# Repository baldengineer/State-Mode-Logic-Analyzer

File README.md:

Every logic analyzer available today samples asychrnously. On slower systems this is needlessly wasteful.

This logic analyzer works as a state mode capture. A clock on the device-under-test (DUT) drives the capture.

More to come...

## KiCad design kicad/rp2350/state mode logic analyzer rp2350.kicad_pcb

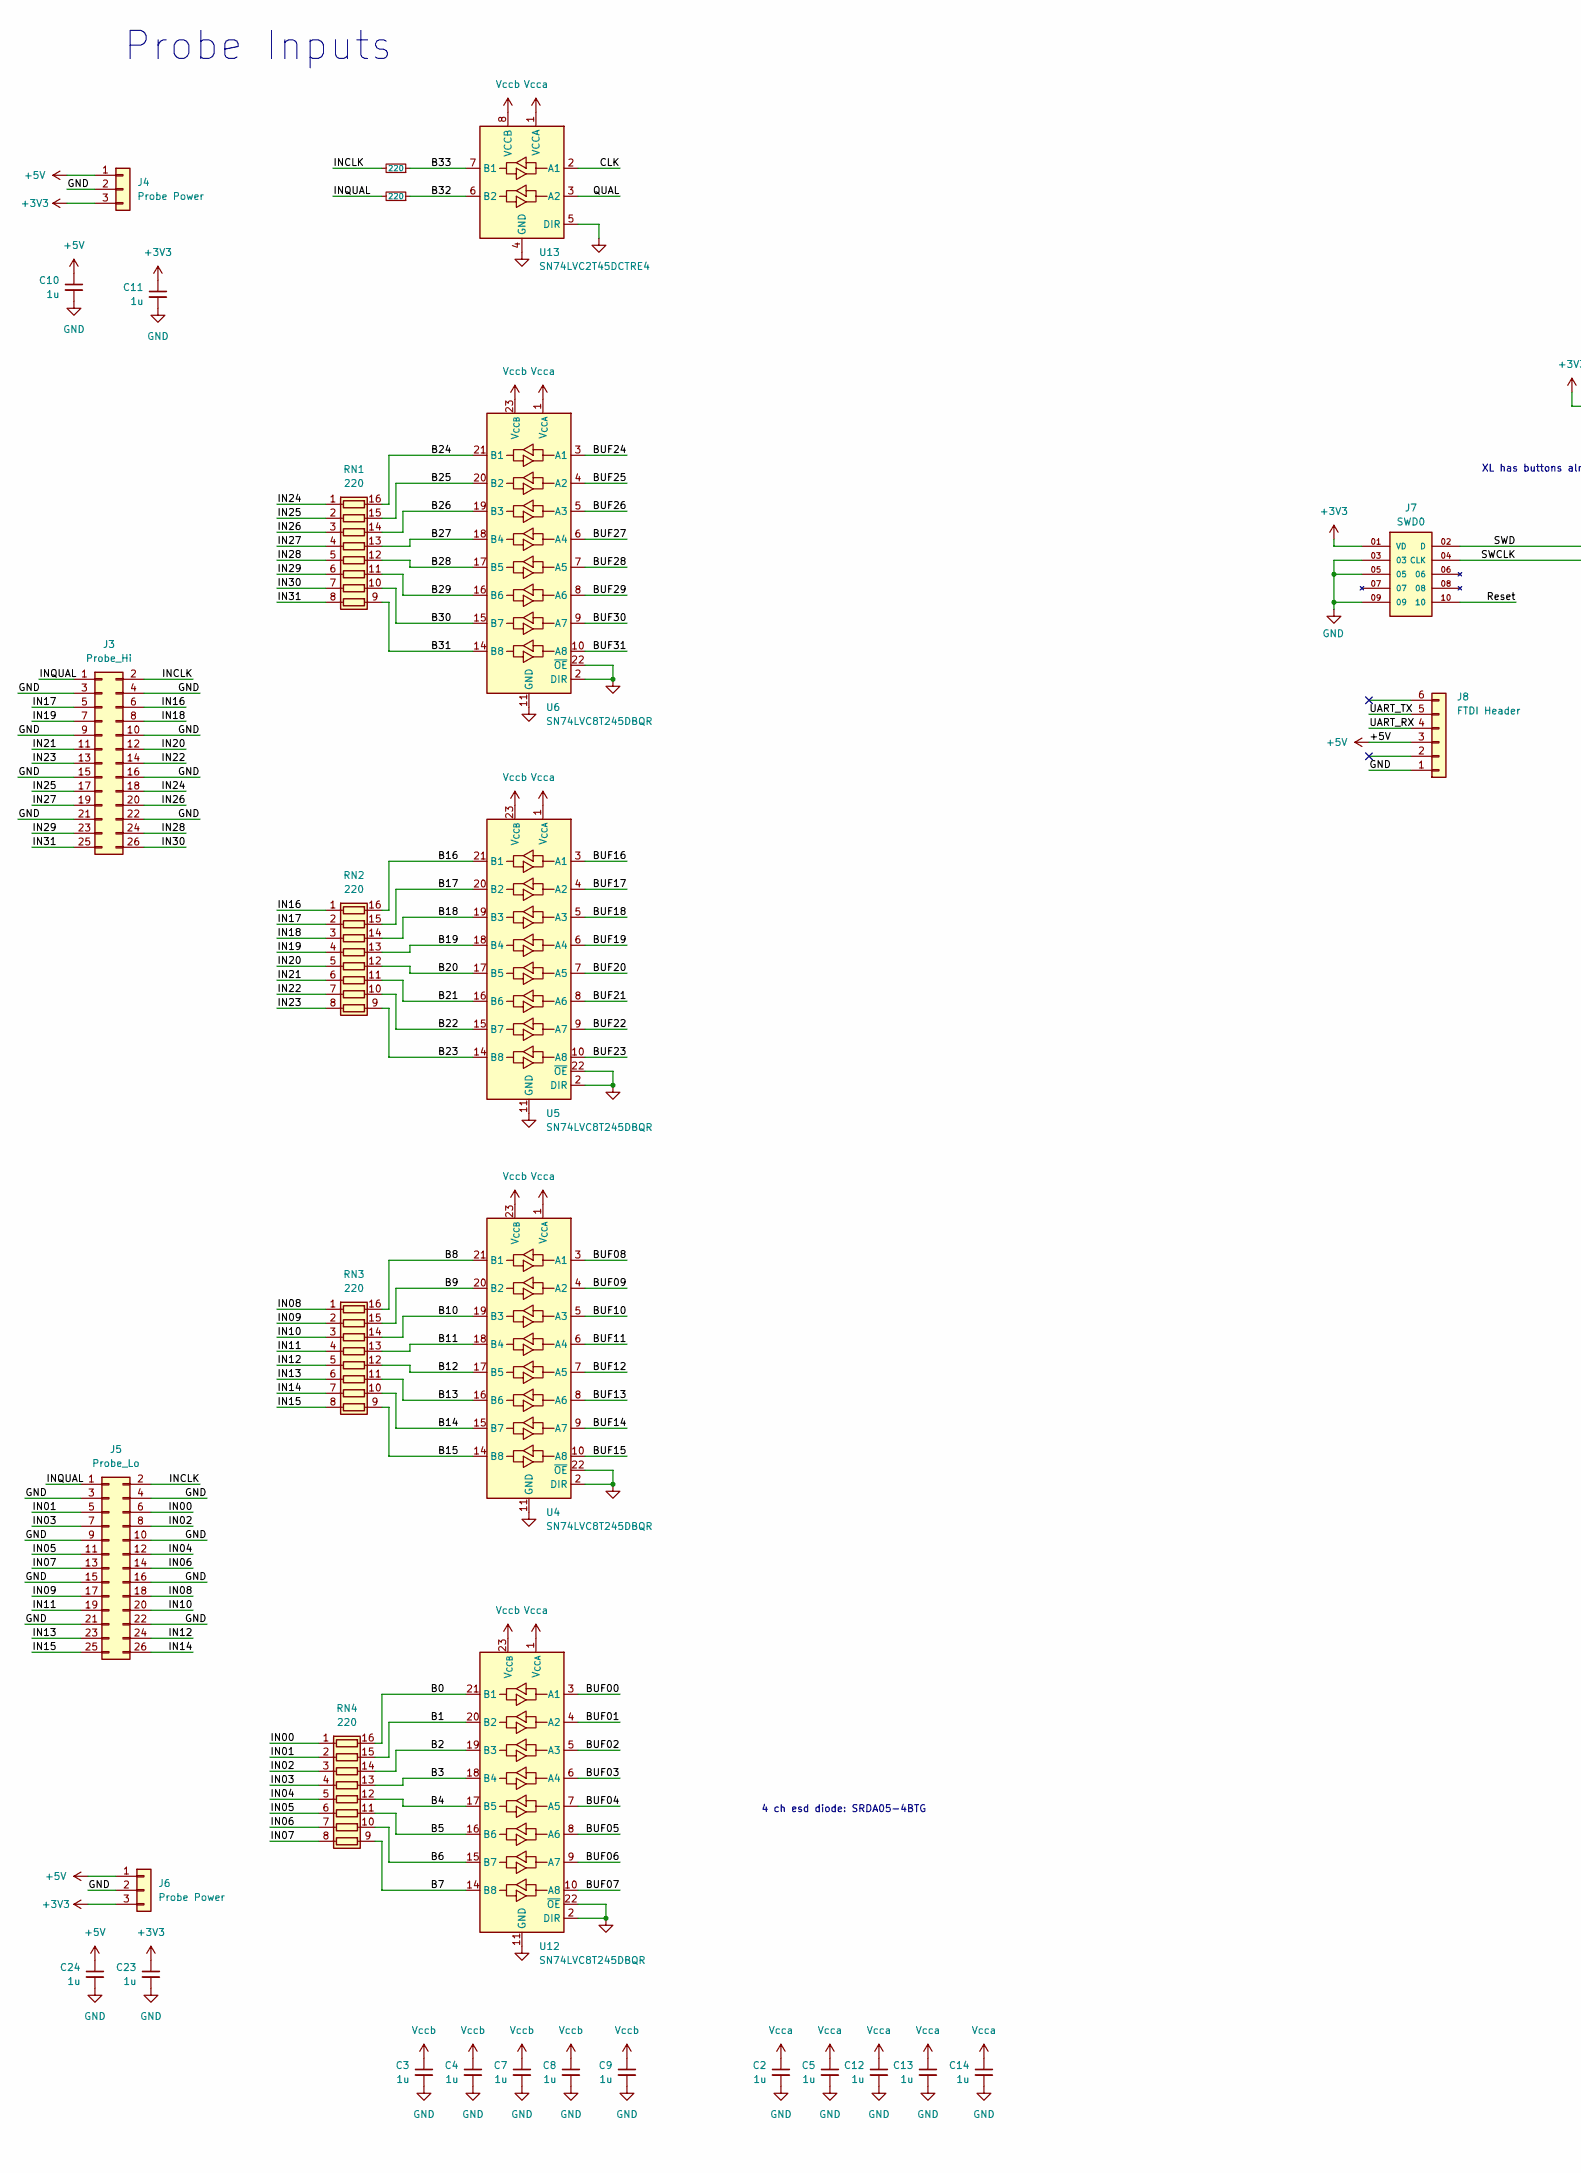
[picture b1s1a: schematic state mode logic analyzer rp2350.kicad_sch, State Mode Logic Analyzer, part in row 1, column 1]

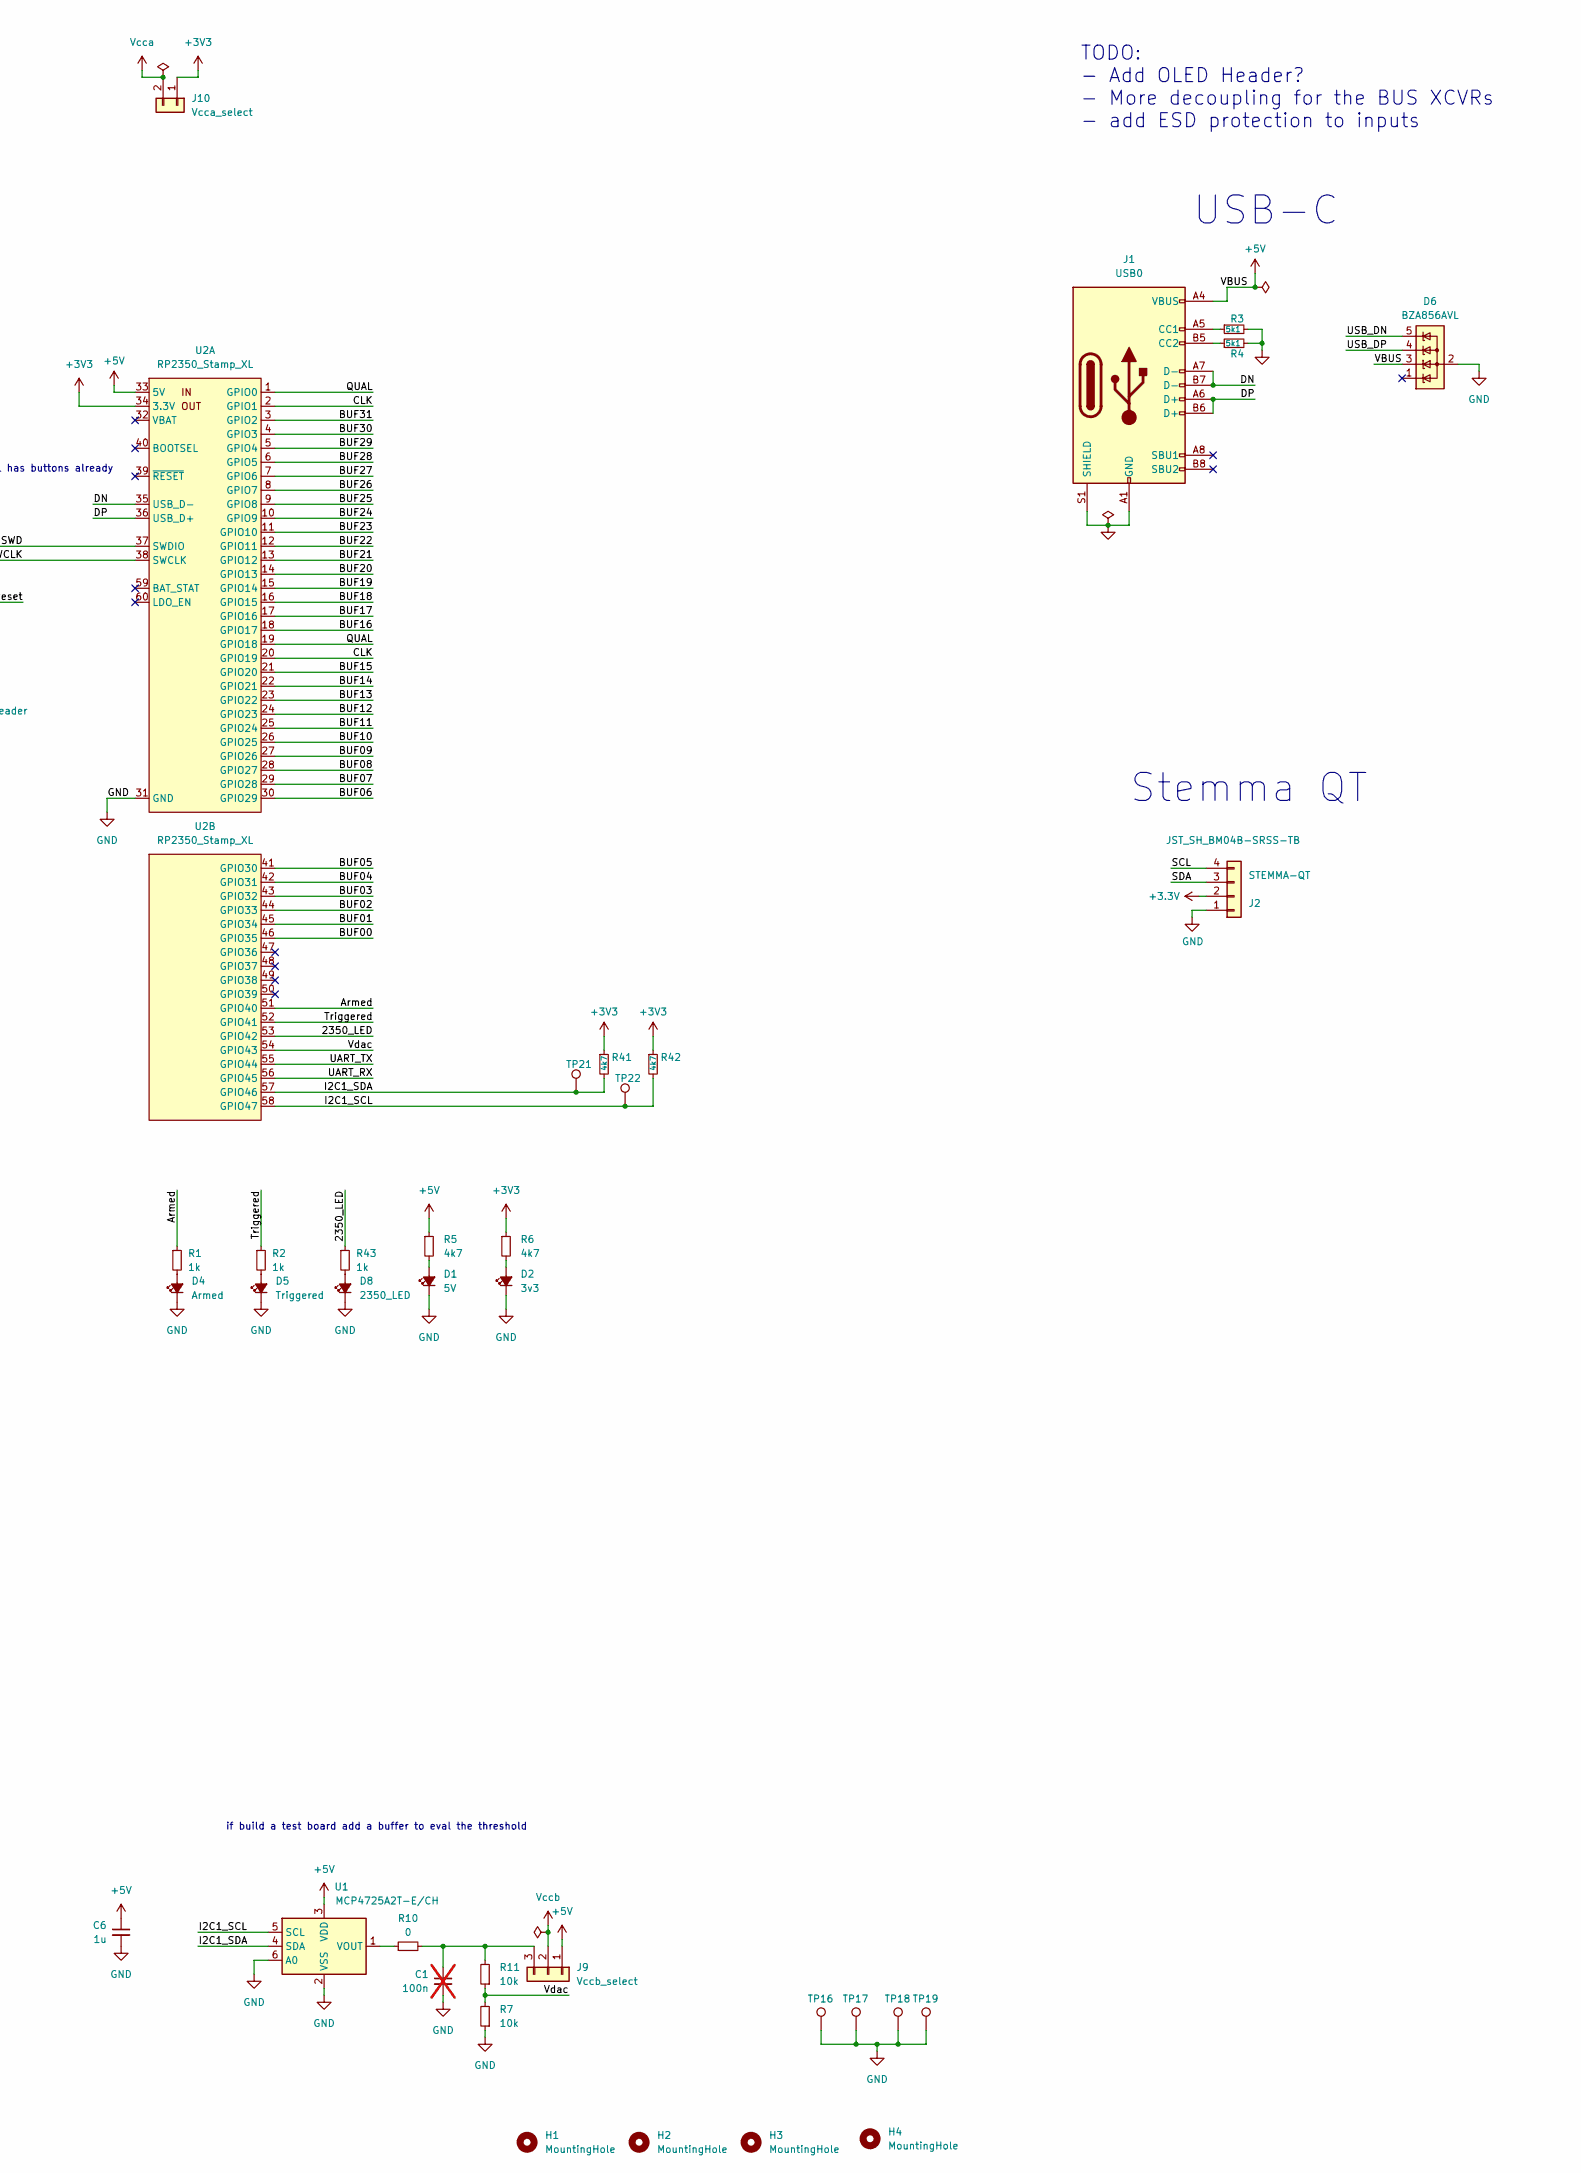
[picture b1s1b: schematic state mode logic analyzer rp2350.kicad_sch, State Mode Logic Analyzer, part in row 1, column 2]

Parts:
C1: 100n; C_0603_1608Metric_Pad1.08x0.95mm_HandSolder; not fitted
C2, C3, C4, C5, C6, C7, C8, C9, C10, C11, C12, C13, C14, C23, C24: 1u; C_0603_1608Metric_Pad1.08x0.95mm_HandSolder
D1: 5V; LED_1206_3216Metric_Pad1.42x1.75mm_HandSolder
D2: 3v3; LED_1206_3216Metric_Pad1.42x1.75mm_HandSolder
D4: Armed; LED_1206_3216Metric_Pad1.42x1.75mm_HandSolder
D5: Triggered; LED_1206_3216Metric_Pad1.42x1.75mm_HandSolder
D6: BZA856AVL; SOT-353_SC-70-5
D8: 2350_LED; LED_1206_3216Metric_Pad1.42x1.75mm_HandSolder
H1, H2, H3, H4: MountingHole; MountingHole_2.7mm
J1: USB0; USB_C_Receptacle_GCT_USB4105-xx-A_16P_TopMnt_Horizontal
J2: JST_SH_BM04B-SRSS-TB; JST_SH_BM04B-SRSS-TB_1x04-1MP_P1.00mm_Vertical
J3: Probe_Hi; PinHeader_2x13_P2.54mm_Vertical
J4, J6: Probe Power; PinHeader_1x03_P2.54mm_Vertical
J5: Probe_Lo; PinHeader_2x13_P2.54mm_Vertical
J7: SWD0; SAMTEC_FTSH-105-XX-X-DV; PARTREV H
J8: FTDI Header; PinSocket_1x06_P2.54mm_Vertical
J9: Vccb_select; PinHeader_1x03_P2.54mm_Vertical
J10: Vcca_select; PinHeader_2x01_P2.54mm_Vertical
R1, R2, R43: 1k; R_0603_1608Metric_Pad0.98x0.95mm_HandSolder
R3, R4: 5k1; R_0603_1608Metric_Pad0.98x0.95mm_HandSolder
R5, R6, R41, R42: 4k7; R_0603_1608Metric_Pad0.98x0.95mm_HandSolder
R7, R11: 10k; R_0603_1608Metric
R10: 0; R_0603_1608Metric
R73, R74: 220; R_0603_1608Metric
RN1, RN2, RN3, RN4: YC248-FR-07220RL; R_Array_Convex_8x0602
TP16, TP17, TP18, TP19, TP21, TP22: TestPoint_Harwin; Harwin-S1751-46-Test-Point
U1: MCP4725A2T-E/CH; SOT-23-6
U2: RP2350_Stamp_XL; RP2xxx_Stamp_XL_THT
U4, U5, U6, U12: SN74LVC8T245DBQR; SSOP-24_3.9x8.7mm_P0.635mm
U13: SN74LVC2T45DCTRE4; SSOP-8_2.95x2.8mm_P0.65mm

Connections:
+3.3V: J2.2
+3V3: C11.1, C23.1, J4.3, J6.3, J7.01 (VD), J10.1, R6.1, R41.1, R42.1, U2.34 (3.3V)
+5V: C6.1, C10.1, C24.1, D6.3 (K), J1.A4 (VBUS), J1.A9 (VBUS), J1.B4 (VBUS), J1.B9 (VBUS), J4.1, J6.1, J8.3, J9.1, R5.1, U1.3 (VDD), U2.33 (5V)
/2350_LED: R43.1, U2.53 (GPIO42)
/Armed: R1.1, U2.51 (GPIO40)
/B0: RN4.16 (R1.2), U12.21 (B1)
/B1: RN4.15 (R2.2), U12.20 (B2)
/B2: RN4.14 (R3.2), U12.19 (B3)
/B3: RN4.13 (R4.2), U12.18 (B4)
/B4: RN4.12 (R5.2), U12.17 (B5)
/B5: RN4.11 (R6.2), U12.16 (B6)
/B6: RN4.10 (R7.2), U12.15 (B7)
/B7: RN4.9 (R8.2), U12.14 (B8)
/B8: RN3.16 (R1.2), U4.21 (B1)
/B9: RN3.15 (R2.2), U4.20 (B2)
/B10: RN3.14 (R3.2), U4.19 (B3)
/B11: RN3.13 (R4.2), U4.18 (B4)
/B12: RN3.12 (R5.2), U4.17 (B5)
/B13: RN3.11 (R6.2), U4.16 (B6)
/B14: RN3.10 (R7.2), U4.15 (B7)
/B15: RN3.9 (R8.2), U4.14 (B8)
/B16: RN2.16 (R1.2), U5.21 (B1)
/B17: RN2.15 (R2.2), U5.20 (B2)
/B18: RN2.14 (R3.2), U5.19 (B3)
/B19: RN2.13 (R4.2), U5.18 (B4)
/B20: RN2.12 (R5.2), U5.17 (B5)
/B21: RN2.11 (R6.2), U5.16 (B6)
/B22: RN2.10 (R7.2), U5.15 (B7)
/B23: RN2.9 (R8.2), U5.14 (B8)
/B24: RN1.16 (R1.2), U6.21 (B1)
/B25: RN1.15 (R2.2), U6.20 (B2)
/B26: RN1.14 (R3.2), U6.19 (B3)
/B27: RN1.13 (R4.2), U6.18 (B4)
/B28: RN1.12 (R5.2), U6.17 (B5)
/B29: RN1.11 (R6.2), U6.16 (B6)
/B30: RN1.10 (R7.2), U6.15 (B7)
/B31: RN1.9 (R8.2), U6.14 (B8)
/B32: R74.1, U13.6 (B2)
/B33: R73.1, U13.7 (B1)
/BUF00: U2.46 (GPIO35), U12.3 (A1)
/BUF01: U2.45 (GPIO34), U12.4 (A2)
/BUF02: U2.44 (GPIO33), U12.5 (A3)
/BUF03: U2.43 (GPIO32), U12.6 (A4)
/BUF04: U2.42 (GPIO31), U12.7 (A5)
/BUF05: U2.41 (GPIO30), U12.8 (A6)
/BUF06: U2.30 (GPIO29), U12.9 (A7)
/BUF07: U2.29 (GPIO28), U12.10 (A8)
/BUF08: U2.28 (GPIO27), U4.3 (A1)
/BUF09: U2.27 (GPIO26), U4.4 (A2)
/BUF10: U2.26 (GPIO25), U4.5 (A3)
/BUF11: U2.25 (GPIO24), U4.6 (A4)
/BUF12: U2.24 (GPIO23), U4.7 (A5)
/BUF13: U2.23 (GPIO22), U4.8 (A6)
/BUF14: U2.22 (GPIO21), U4.9 (A7)
/BUF15: U2.21 (GPIO20), U4.10 (A8)
/BUF16: U2.18 (GPIO17), U5.3 (A1)
/BUF17: U2.17 (GPIO16), U5.4 (A2)
/BUF18: U2.16 (GPIO15), U5.5 (A3)
/BUF19: U2.15 (GPIO14), U5.6 (A4)
/BUF20: U2.14 (GPIO13), U5.7 (A5)
/BUF21: U2.13 (GPIO12), U5.8 (A6)
/BUF22: U2.12 (GPIO11), U5.9 (A7)
/BUF23: U2.11 (GPIO10), U5.10 (A8)
/BUF24: U2.10 (GPIO9), U6.3 (A1)
/BUF25: U2.9 (GPIO8), U6.4 (A2)
/BUF26: U2.8 (GPIO7), U6.5 (A3)
/BUF27: U2.7 (GPIO6), U6.6 (A4)
/BUF28: U2.6 (GPIO5), U6.7 (A5)
/BUF29: U2.5 (GPIO4), U6.8 (A6)
/BUF30: U2.4 (GPIO3), U6.9 (A7)
/BUF31: U2.3 (GPIO2), U6.10 (A8)
/CLK: U2.2 (GPIO1), U2.20 (GPIO19), U13.2 (A1)
/DN: J1.A7 (D-), J1.B7 (D-), U2.35 (USB_D-)
/DP: J1.A6 (D+), J1.B6 (D+), U2.36 (USB_D+)
/I2C1_SCL: R42.2, TP22.1, U1.5 (SCL), U2.58 (GPIO47)
/I2C1_SDA: R41.2, TP21.1, U1.4 (SDA), U2.57 (GPIO46)
/IN00: J5.6, RN4.1 (R1.1)
/IN01: J5.5, RN4.2 (R2.1)
/IN02: J5.8, RN4.3 (R3.1)
/IN03: J5.7, RN4.4 (R4.1)
/IN04: J5.12, RN4.5 (R5.1)
/IN05: J5.11, RN4.6 (R6.1)
/IN06: J5.14, RN4.7 (R7.1)
/IN07: J5.13, RN4.8 (R8.1)
/IN08: J5.18, RN3.1 (R1.1)
/IN09: J5.17, RN3.2 (R2.1)
/IN10: J5.20, RN3.3 (R3.1)
/IN11: J5.19, RN3.4 (R4.1)
/IN12: J5.24, RN3.5 (R5.1)
/IN13: J5.23, RN3.6 (R6.1)
/IN14: J5.26, RN3.7 (R7.1)
/IN15: J5.25, RN3.8 (R8.1)
/IN16: J3.6, RN2.1 (R1.1)
/IN17: J3.5, RN2.2 (R2.1)
/IN18: J3.8, RN2.3 (R3.1)
/IN19: J3.7, RN2.4 (R4.1)
/IN20: J3.12, RN2.5 (R5.1)
/IN21: J3.11, RN2.6 (R6.1)
/IN22: J3.14, RN2.7 (R7.1)
/IN23: J3.13, RN2.8 (R8.1)
/IN24: J3.18, RN1.1 (R1.1)
/IN25: J3.17, RN1.2 (R2.1)
/IN26: J3.20, RN1.3 (R3.1)
/IN27: J3.19, RN1.4 (R4.1)
/IN28: J3.24, RN1.5 (R5.1)
/IN29: J3.23, RN1.6 (R6.1)
/IN30: J3.26, RN1.7 (R7.1)
/IN31: J3.25, RN1.8 (R8.1)
/INCLK: J3.2, J5.2, R73.2
/INQUAL: J3.1, J5.1, R74.2
/QUAL: U2.1 (GPIO0), U2.19 (GPIO18), U13.3 (A2)
/Reset: J7.10
/SCL: J2.4
/SDA: J2.3
/SWCLK: J7.04 (CLK), U2.38 (SWCLK)
/SWD: J7.02 (D), U2.37 (SWDIO)
/Triggered: R2.1, U2.52 (GPIO41)
/UART_RX: J8.4, U2.56 (GPIO45)
/UART_TX: J8.5, U2.55 (GPIO44)
/USB_DN: D6.5 (K)
/USB_DP: D6.4 (K)
/Vdac: R7.2, R11.1, U2.54 (GPIO43)
GND: C1.2, C2.2, C3.2, C4.2, C5.2, C6.2, C7.2, C8.2, C9.2, C10.2, C11.2, C12.2, C13.2, C14.2, C23.2, C24.2, D1.1 (K), D2.1 (K), D4.1 (K), D5.1 (K), D6.2 (A), D8.1 (K), J1.A1 (GND), J1.A12 (GND), J1.B1 (GND), J1.B12 (GND), J1.S1 (SHIELD), J2.1, J3.3, J3.4, J3.9, J3.10, J3.15, J3.16, J3.21, J3.22, J4.2, J5.3, J5.4, J5.9, J5.10, J5.15, J5.16, J5.21, J5.22, J6.2, J7.03, J7.05, J7.09, J8.1, R3.2, R4.2, R7.1, TP16.1, TP17.1, TP18.1, TP19.1, U1.2 (VSS), U1.6 (A0), U2.31 (GND), U4.2 (DIR), U4.11 (GND), U4.12 (GND), U4.13 (GND), U4.22 (~OE), U5.2 (DIR), U5.11 (GND), U5.12 (GND), U5.13 (GND), U5.22 (~OE), U6.2 (DIR), U6.11 (GND), U6.12 (GND), U6.13 (GND), U6.22 (~OE), U12.2 (DIR), U12.11 (GND), U12.12 (GND), U12.13 (GND), U12.22 (~OE), U13.4 (GND), U13.5 (DIR)
unnamed: D1.2 (A), R5.2
unnamed: D2.2 (A), R6.2
unnamed: D4.2 (A), R1.2
unnamed: D5.2 (A), R2.2
unnamed: D8.2 (A), R43.2
unnamed: J1.A5 (CC1), R3.1
unnamed: J1.B5 (CC2), R4.1
unnamed: C1.1, J9.3, R10.2, R11.2
unnamed: R10.1, U1.1 (VOUT)
Vcca: C2.1, C5.1, C12.1, C13.1, C14.1, J10.2, U4.1 (V_{CCA}), U5.1 (V_{CCA}), U6.1 (V_{CCA}), U12.1 (V_{CCA}), U13.1 (VCCA)
Vccb: C3.1, C4.1, C7.1, C8.1, C9.1, J9.2, U4.23 (V_{CCB}), U4.24 (V_{CCB}), U5.23 (V_{CCB}), U5.24 (V_{CCB}), U6.23 (V_{CCB}), U6.24 (V_{CCB}), U12.23 (V_{CCB}), U12.24 (V_{CCB}), U13.8 (VCCB)

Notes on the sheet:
TODO: - Add OLED Header? - More decoupling for the BUS XCVRs - add ESD protection to inputs
XL has buttons already
if build a test board add a buffer to eval the threshold
Stemma QT
4 ch esd diode: SRDA05-4BTG
Probe Inputs
USB-C

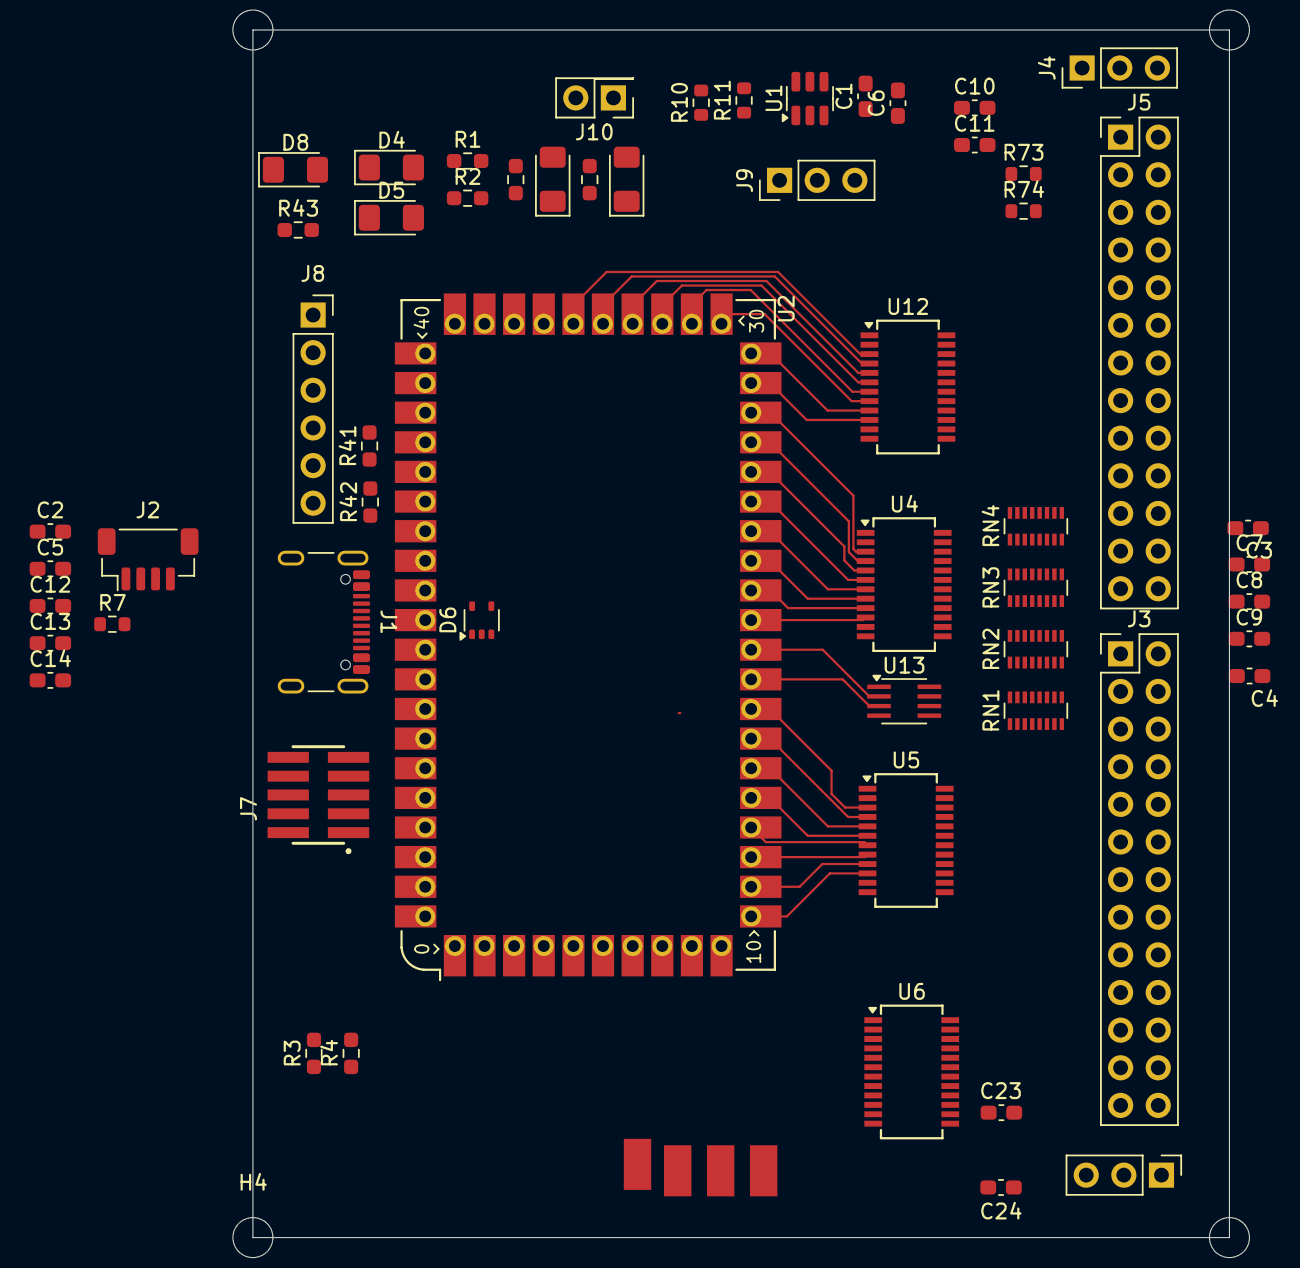
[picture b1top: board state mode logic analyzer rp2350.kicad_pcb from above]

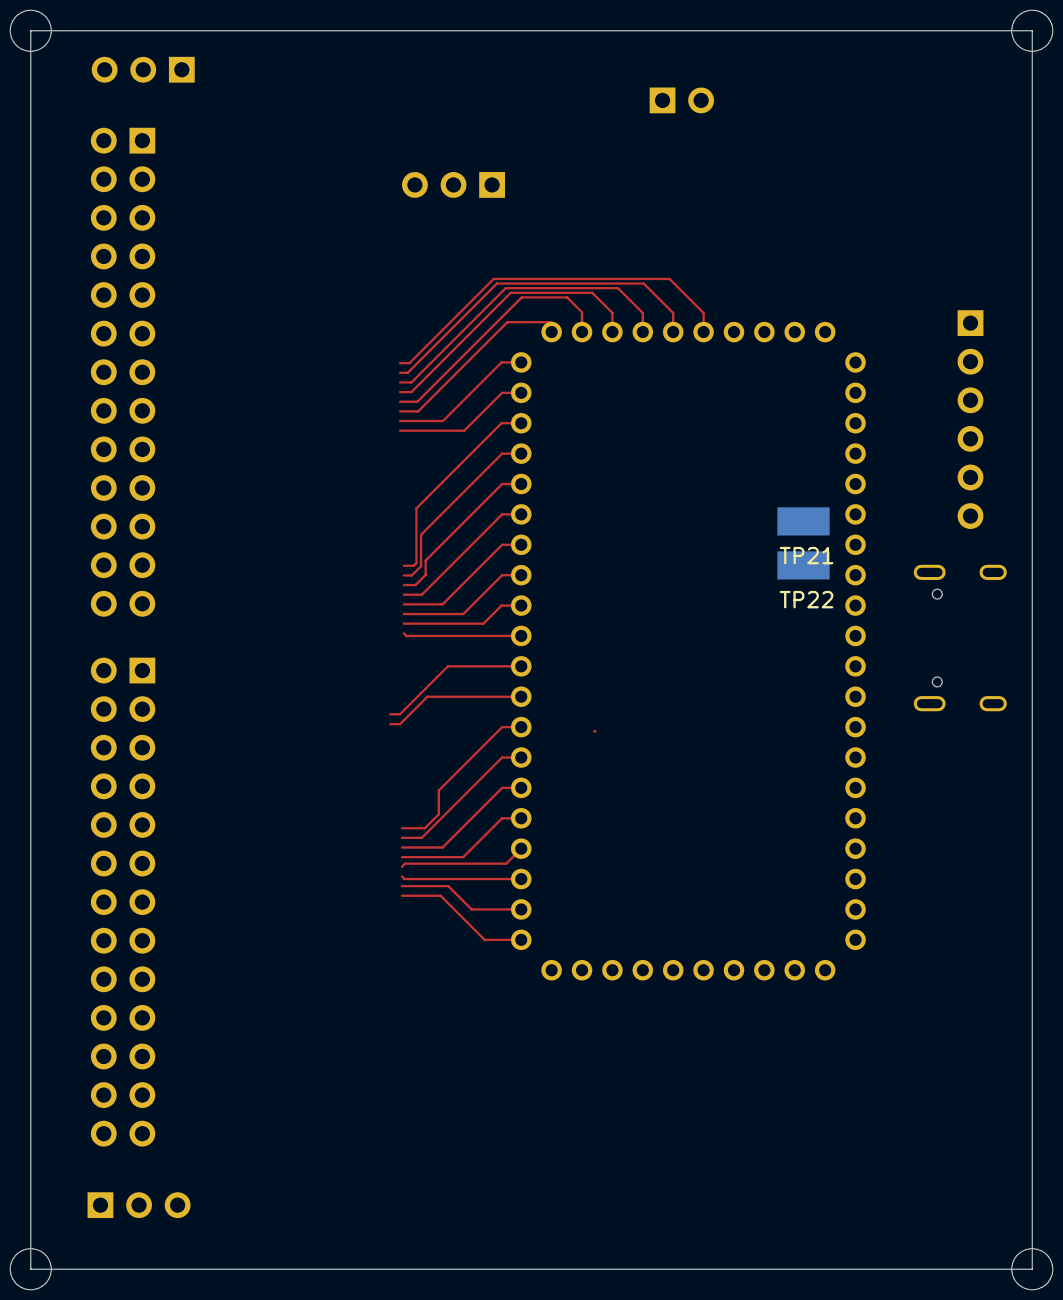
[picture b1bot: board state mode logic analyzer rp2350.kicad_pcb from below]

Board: 4 copper layers, 65.9 x 81.5 mm, 67 parts (2 on the bottom side), 128 nets.

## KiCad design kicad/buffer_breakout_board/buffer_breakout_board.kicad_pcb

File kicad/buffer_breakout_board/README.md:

## Buffer Breakout
A breakout of a dual-supply LVC245 buffer. This board will allow testing current consumption when used with the DAC breakout.

## Status
Rev 1 sent to fab.

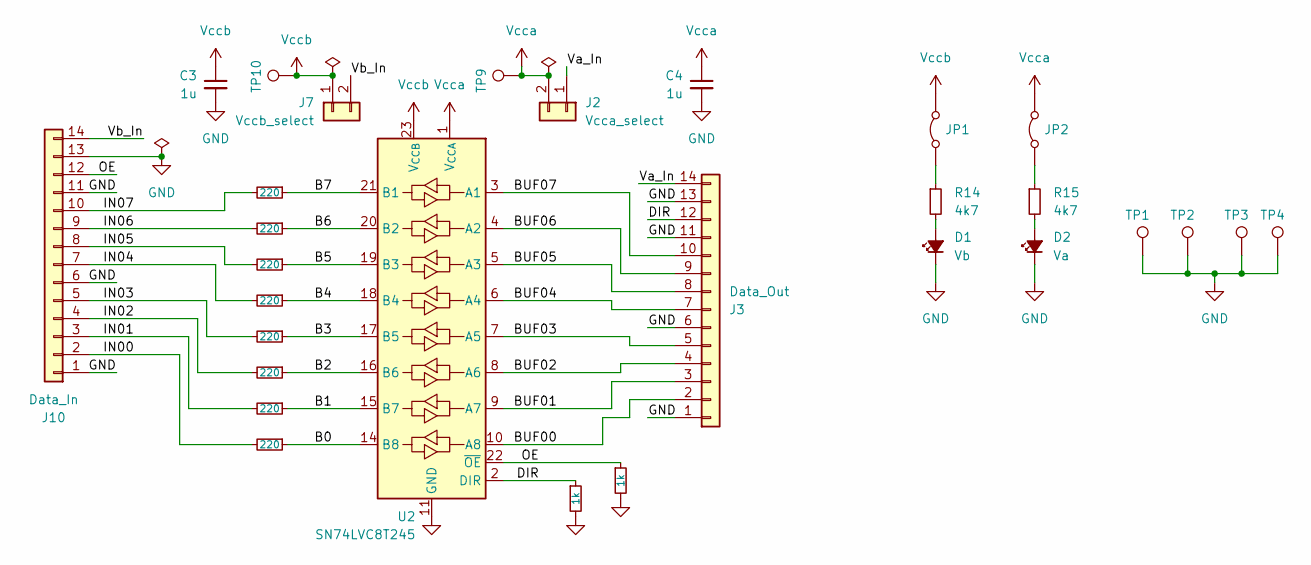
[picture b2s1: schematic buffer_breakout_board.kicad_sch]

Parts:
C3, C4: 1u; C_0603_1608Metric_Pad1.08x0.95mm_HandSolder
D1: Vb; LED_1206_3216Metric_Pad1.42x1.75mm_HandSolder
D2: Va; LED_1206_3216Metric_Pad1.42x1.75mm_HandSolder
J2: Vcca_select; PinHeader_2x01_P2.54mm_Vertical
J3: Data_Out; PinHeader_1x14_P2.54mm_Vertical
J7: Vccb_select; PinHeader_2x01_P2.54mm_Vertical
J10: Data_In; PinHeader_1x14_P2.54mm_Vertical
JP1, JP2: Jumper_2_Bridged; SolderJumper-2_P1.3mm_Bridged_RoundedPad1.0x1.5mm
R1, R2: 1k; R_0603_1608Metric
R4, R5, R6, R7, R8, R9, R10, R11: 220; R_0603_1608Metric
R14, R15: 4k7; R_0603_1608Metric_Pad0.98x0.95mm_HandSolder
TP1, TP2, TP3, TP4, TP9, TP10: TestPoint_Harwin; Harwin-S1751-46-Test-Point
U2: SN74LVC8T245; SSOP-24_3.9x8.7mm_P0.635mm

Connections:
/B0: R11.1, U2.14 (B8)
/B1: R10.1, U2.15 (B7)
/B2: R9.1, U2.16 (B6)
/B3: R8.1, U2.17 (B5)
/B4: R7.1, U2.18 (B4)
/B5: R6.1, U2.19 (B3)
/B6: R5.1, U2.20 (B2)
/B7: R4.1, U2.21 (B1)
/BUF00: J3.2, U2.10 (A8)
/BUF01: J3.3, U2.9 (A7)
/BUF02: J3.4, U2.8 (A6)
/BUF03: J3.5, U2.7 (A5)
/BUF04: J3.7, U2.6 (A4)
/BUF05: J3.8, U2.5 (A3)
/BUF06: J3.9, U2.4 (A2)
/BUF07: J3.10, U2.3 (A1)
/DIR: J3.12, R1.1, U2.2 (DIR)
/IN00: J10.2, R11.2
/IN01: J10.3, R10.2
/IN02: J10.4, R9.2
/IN03: J10.5, R8.2
/IN04: J10.7, R7.2
/IN05: J10.8, R6.2
/IN06: J10.9, R5.2
/IN07: J10.10, R4.2
/OE: J10.12, R2.1, U2.22 (~OE)
/Va_In: J2.1, J3.14
/Vb_In: J7.2, J10.14
GND: C3.2, C4.2, D1.1 (K), D2.1 (K), J3.1, J3.6, J3.11, J3.13, J10.1, J10.6, J10.11, J10.13, R1.2, R2.2, TP1.1, TP2.1, TP3.1, TP4.1, U2.11 (GND), U2.12 (GND), U2.13 (GND)
unnamed: D1.2 (A), R14.2
unnamed: D2.2 (A), R15.2
unnamed: JP1.1 (A), R14.1
unnamed: JP2.1 (A), R15.1
Vcca: C4.1, J2.2, JP2.2 (B), TP9.1, U2.1 (V_{CCA})
Vccb: C3.1, J7.1, JP1.2 (B), TP10.1, U2.23 (V_{CCB}), U2.24 (V_{CCB})

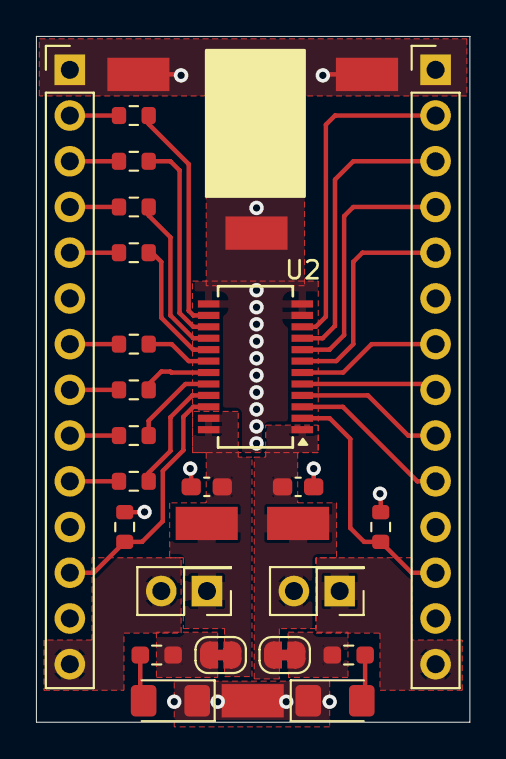
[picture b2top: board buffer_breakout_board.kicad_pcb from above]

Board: 2 copper layers, 24.1 x 38.1 mm, 30 parts (1 on the bottom side), 35 nets.

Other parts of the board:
kibuzzard-67318B48: G***; kibuzzard-67318B48

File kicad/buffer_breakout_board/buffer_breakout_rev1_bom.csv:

"Reference","Value","Datasheet","Footprint","Qty","DNP"
"C3,C4","1u","~","Capacitor_SMD:C_0603_1608Metric_Pad1.08x0.95mm_HandSolder","2",""
"D1","Vb","~","LED_SMD:LED_1206_3216Metric_Pad1.42x1.75mm_HandSolder","1",""
"D2","Va","~","LED_SMD:LED_1206_3216Metric_Pad1.42x1.75mm_HandSolder","1",""
"J2","Vcca_select","~","Connector_PinHeader_2.54mm:PinHeader_2x01_P2.54mm_Vertical","1",""
"J3","Data_Out","~","Connector_PinHeader_2.54mm:PinHeader_1x14_P2.54mm_Vertical","1",""
"J7","Vccb_select","~","Connector_PinHeader_2.54mm:PinHeader_2x01_P2.54mm_Vertical","1",""
"J10","Data_In","~","Connector_PinHeader_2.54mm:PinHeader_1x14_P2.54mm_Vertical","1",""
"JP1,JP2","Jumper_2_Bridged","~","Jumper:SolderJumper-2_P1.3mm_Bridged_RoundedPad1.0x1.5mm","2",""
"R1,R2","1k","~","Resistor_SMD:R_0603_1608Metric","2",""
"R4,R5,R6,R7,R8,R9,R10,R11","220","~","Resistor_SMD:R_0603_1608Metric","8",""
"R14,R15","4k7","~","Resistor_SMD:R_0603_1608Metric_Pad0.98x0.95mm_HandSolder","2",""
"TP1,TP2,TP3,TP4,TP9,TP10","TestPoint_Harwin","~","My Libraries:Harwin-S1751-46-Test-Point","6",""
"U2","SN74LVC8T245DBQR","https://www.ti.com/lit/ds/symlink/sn74lvc8t245.pdf","Package_SO:SSOP-24_3.9x8.7mm_P0.635mm","1",""

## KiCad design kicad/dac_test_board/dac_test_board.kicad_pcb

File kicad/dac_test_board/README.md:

## DAC Test Board
This board is to test current drive capability of a [Microchip MCP7425](https://www.microchip.com/en-us/product/mcp4725) 12-bit DAC. It drives the Vcc of the dual-supply buffer. The idea is to use this DAC to vary the VCC to vary the Vthreshold.

## Status
Rev 1 sent to fab.

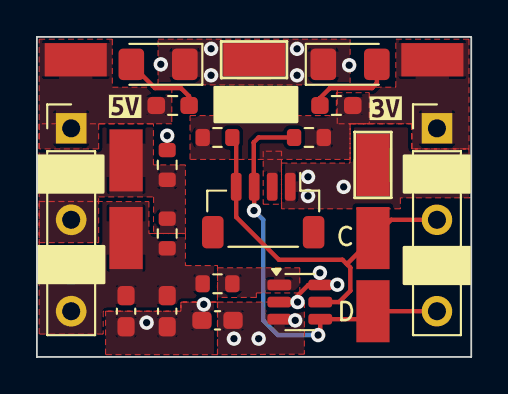
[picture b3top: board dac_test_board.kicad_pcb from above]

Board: 2 copper layers, 24.1 x 17.8 mm, 27 parts (1 on the bottom side), 10 nets.

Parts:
C1, C4: 1u; C_0603_1608Metric_Pad1.08x0.95mm_HandSolder
C2: 100n; C_0603_1608Metric_Pad1.08x0.95mm_HandSolder
D1: 5V; LED_1206_3216Metric_Pad1.42x1.75mm_HandSolder
D2: 3v3; LED_1206_3216Metric_Pad1.42x1.75mm_HandSolder
J2: Vout; PinHeader_1x05_P2.54mm_Vertical
J4: I2C; PinHeader_1x05_P2.54mm_Vertical
J8: JST_SH_BM04B-SRSS-TB; JST_SH_BM04B-SRSS-TB_1x04-1MP_P1.00mm_Vertical
R1: 0; R_0603_1608Metric
R2, R3, R12, R13: 10k; R_0603_1608Metric
R14, R15: 4k7; R_0603_1608Metric_Pad0.98x0.95mm_HandSolder
TP2, TP4, TP5, TP6, TP7, TP8, TP11, TP12: TestPoint_Harwin; Harwin-S1751-46-Test-Point
U1: MCP4725A2T-E/CH; SOT-23-6
kibuzzard-67311A27: G***; kibuzzard-67311A27
kibuzzard-67311A33: G***; kibuzzard-67311A33
kibuzzard-67311944: G***; kibuzzard-67311944

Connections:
+3V3: J4.1, J8.2, R12.2, R13.2, R15.1, TP7.1
+5V: C1.1, J2.1, R14.1, TP6.1, U1.3 (VDD)
/I2C1_SCL: J4.3, J8.4, R12.1, TP11.1, U1.5 (SCL)
/I2C1_SDA: J4.5, J8.3, R13.1, TP12.1, U1.4 (SDA)
/Vdac_half: J2.3, R2.1, R3.2, TP8.1
GND: C1.2, C2.2, C4.2, D1.1 (K), D2.1 (K), J2.2, J2.4, J4.2, J4.4, J8.1, R3.1, TP2.1, TP4.1, U1.2 (VSS), U1.6 (A0)
unnamed: D1.2 (A), R14.2
unnamed: D2.2 (A), R15.2
unnamed: R1.1, U1.1 (VOUT)
Vdac_out: C2.1, C4.1, J2.5, R1.2, R2.2, TP5.1

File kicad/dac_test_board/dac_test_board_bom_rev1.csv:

"Reference","Value","Datasheet","Footprint","Qty","DNP"
"C1","1u","~","Capacitor_SMD:C_0603_1608Metric_Pad1.08x0.95mm_HandSolder","1",""
"C2","100n","~","Capacitor_SMD:C_0603_1608Metric_Pad1.08x0.95mm_HandSolder","1","DNP"
"C4","1u","~","Capacitor_SMD:C_0603_1608Metric_Pad1.08x0.95mm_HandSolder","1","DNP"
"D1","5V","~","LED_SMD:LED_1206_3216Metric_Pad1.42x1.75mm_HandSolder","1",""
"D2","3v3","~","LED_SMD:LED_1206_3216Metric_Pad1.42x1.75mm_HandSolder","1",""
"J2","Vout","~","Connector_PinHeader_2.54mm:PinHeader_1x05_P2.54mm_Vertical","1",""
"J4","I2C","~","Connector_PinHeader_2.54mm:PinHeader_1x05_P2.54mm_Vertical","1",""
"J8","JST_SH_BM04B-SRSS-TB","~","Connector_JST:JST_SH_BM04B-SRSS-TB_1x04-1MP_P1.00mm_Vertical","1",""
"R1","0","~","Resistor_SMD:R_0603_1608Metric","1",""
"R2,R3","10k","~","Resistor_SMD:R_0603_1608Metric","2",""
"R12,R13","10k","~","Resistor_SMD:R_0603_1608Metric","2","DNP"
"R14,R15","4k7","~","Resistor_SMD:R_0603_1608Metric_Pad0.98x0.95mm_HandSolder","2",""
"TP2,TP4,TP5,TP6,TP7,TP8,TP11,TP12","TestPoint_Harwin","~","My Libraries:Harwin-S1751-46-Test-Point","8",""
"U1","MCP4725A2T-E/CH","http://ww1.microchip.com/downloads/en/DeviceDoc/22039d.pdf","Package_TO_SOT_SMD:SOT-23-6","1",""
